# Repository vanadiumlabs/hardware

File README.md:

hardware
========

Boards, parts and firmware

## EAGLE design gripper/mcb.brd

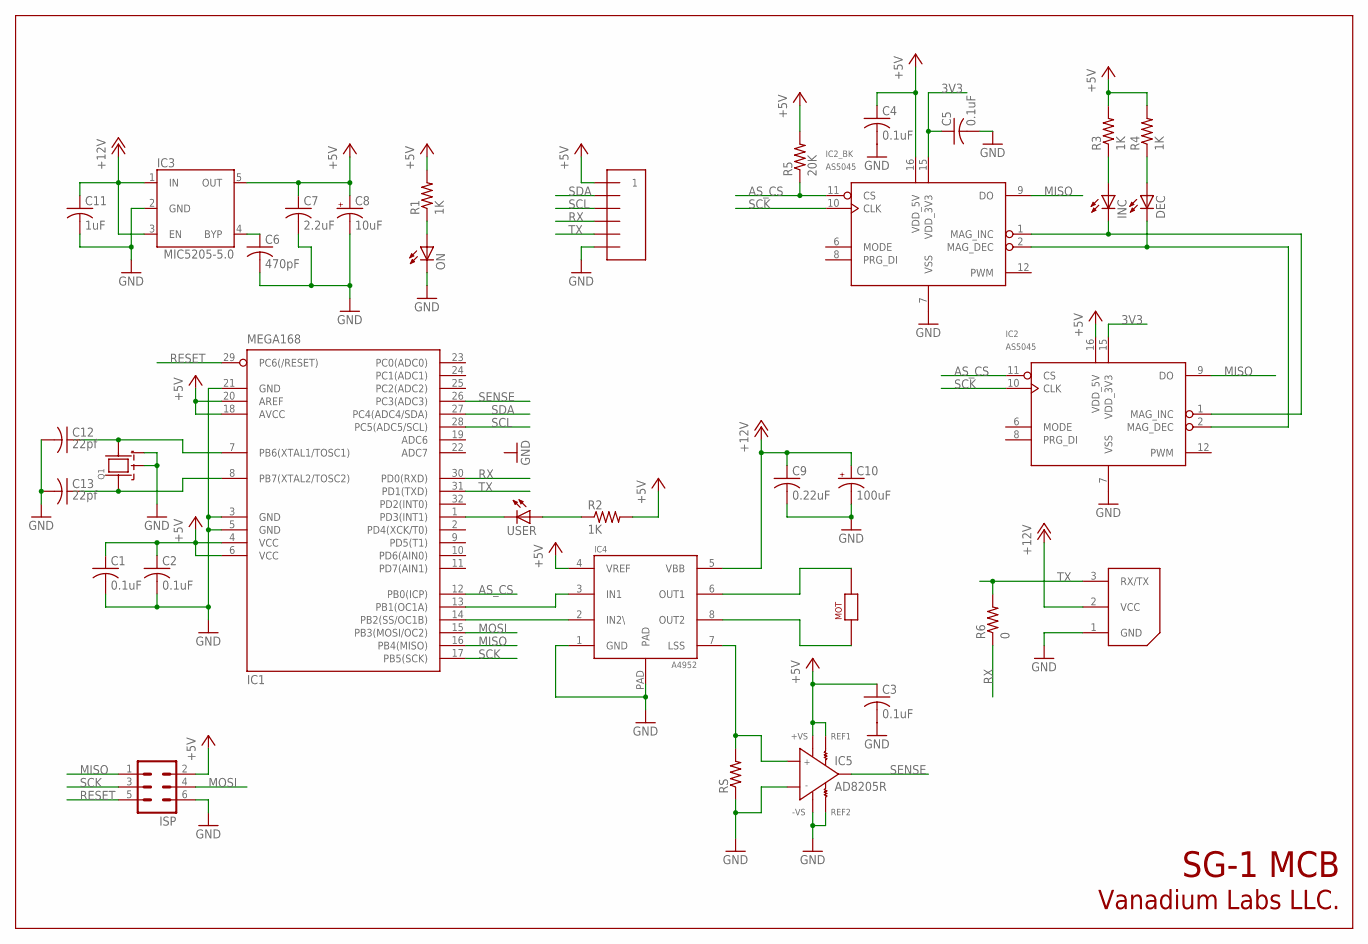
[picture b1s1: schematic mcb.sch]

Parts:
C1, C2, C3, C4, C5: 0.1uF; C0603
C6: 470pF; C0603
C7: 2.2uF; C0603
C8: 10uF; PANASONIC_B
C9: 0.22uF; C0603
C10: 100uF; PANASONIC_B
C11: 1uF; C0603
C12, C13: 22pf; C0603
DEC: LEDCHIPLED_0603; CHIPLED_0603
IC1: MEGA168; TQFP32-08
IC2, IC2_BK: AS5045; SSOP16
IC3: MIC5205-5.0; SOT-23-5
IC4: A4952; SOIC8TP
IC5: AD8205R; SO8
INC: LEDCHIPLED_0603; CHIPLED_0603
ISP: MA03-2
MOT: JUMPER; 2-PIN
ON: LEDCHIPLED_0603; CHIPLED_0603
Q1: 16MHZ; 4LCC
R1, R2, R3, R4: 1K; R0603
R5: 20K; R0603
R6: 0; R0603
RS: R-US_R1206; R1206
U$2: HEADER6; 1X6
U$5: AX-12; WM18887-ND
USER: LEDCHIPLED_0603; CHIPLED_0603

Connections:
3V3: C5.1, IC2.15 (VDD_3V3), IC2_BK.15 (VDD_3V3)
+5V: C1.1, C2.1, C3.1, C4.1, C7.1, C8.+, IC1.4 (VCC), IC1.6 (VCC), IC1.18 (AVCC), IC1.20 (AREF), IC2.16 (VDD_5V), IC2_BK.16 (VDD_5V), IC3.5 (OUT), IC4.4 (VREF), IC5.6 (+VS), IC5.7 (REF1), ISP.2, R1.2, R2.2, R3.2, R4.2, R5.2, U$2.P$1 (1)
+12V: C9.1, C10.+, C11.1, IC3.1 (IN), IC3.3 (EN), IC4.5 (VBB), U$5.2 (VCC)
AS_CS: IC1.12 (PB0(ICP)), IC2.11 (CS), IC2_BK.11 (CS), R5.1
GND: C1.2, C2.2, C3.2, C4.2, C5.2, C6.2, C7.2, C8.-, C9.2, C10.-, C11.2, C12.2, C13.2, IC1.3 (GND), IC1.5 (GND), IC1.21 (GND), IC2.7 (VSS), IC2_BK.7 (VSS), IC3.2 (GND), IC4.1 (GND), IC4.PAD, IC5.1 (IN-), IC5.2 (-VS), IC5.3 (REF2), ISP.6, ON.C, Q1.2 (G1), Q1.4 (G2), RS.1, U$2.P$6, U$5.1 (GND)
MISO: IC1.16 (PB4(MISO)), IC2.9 (DO), IC2_BK.9 (DO), ISP.1
MOSI: IC1.15 (PB3(MOSI/OC2)), ISP.4
unnamed: IC4.6 (OUT1), MOT.P$2
unnamed: IC4.8 (OUT2), MOT.P$1
unnamed: IC4.7 (LSS), IC5.8 (IN+), RS.2
unnamed: IC1.1 (PD3(INT1)), USER.C
unnamed: IC2.1 (MAG_INC), IC2_BK.1 (MAG_INC), INC.C
unnamed: DEC.C, IC2.2 (MAG_DEC), IC2_BK.2 (MAG_DEC)
unnamed: INC.A, R3.1
unnamed: DEC.A, R4.1
unnamed: C12.1, IC1.7 (PB6(XTAL1/TOSC1)), Q1.3
unnamed: C13.1, IC1.8 (PB7(XTAL2/TOSC2)), Q1.1
unnamed: IC1.14 (PB2(SS/OC1B)), IC4.2 (IN2\)
unnamed: ON.A, R1.1
unnamed: R2.1, USER.A
unnamed: IC1.13 (PB1(OC1A)), IC4.3 (IN1)
unnamed: C6.1, IC3.4 (BYP)
RESET: IC1.29 (PC6(/RESET)), ISP.5
RX: IC1.30 (PD0(RXD)), R6.1, U$2.P$4
SCK: IC1.17 (PB5(SCK)), IC2.10 (CLK), IC2_BK.10 (CLK), ISP.3
SCL: IC1.28 (PC5(ADC5/SCL)), U$2.P$3
SDA: IC1.27 (PC4(ADC4/SDA)), U$2.P$2
SENSE: IC1.26 (PC3(ADC3)), IC5.5 (OUT)
TX: IC1.31 (PD1(TXD)), R6.2, U$2.P$5, U$5.3 (RX/TX)

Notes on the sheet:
Vanadium Labs LLC.
SG-1 MCB

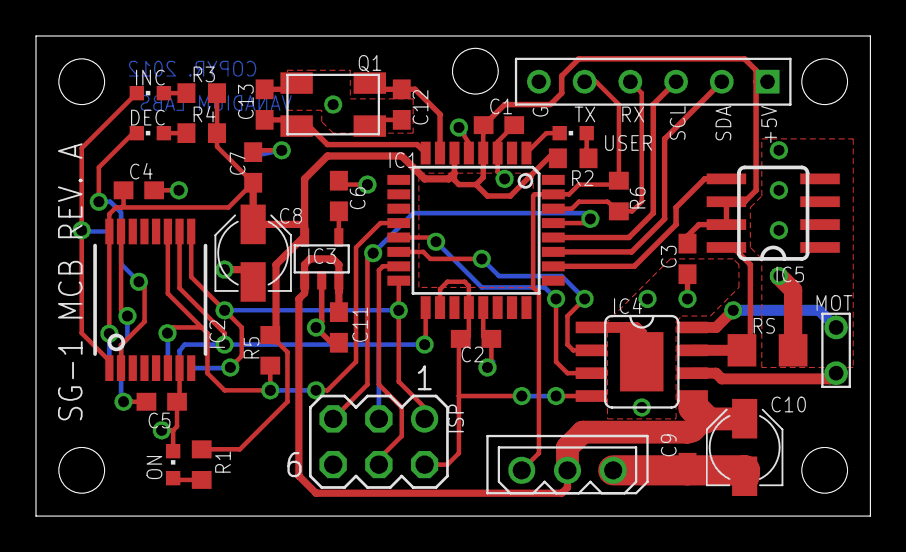
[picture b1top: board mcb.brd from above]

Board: 2 copper layers, 46.4 x 26.7 mm, 35 parts (1 on the bottom side), 29 nets.

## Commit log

2013-02-02 import from svn
2014-07-02 check in old arbotix design
2014-07-02 check in commander design
2014-07-02 check in rxbridge design
2014-07-02 check in servostik design
2014-07-04 add board layout and BOM
2014-07-04 add a readme for the ax-m1
2014-07-04 add readme
2014-07-04 add license
2014-07-04 check in rev B and gerbers
2014-09-29 add schematic and board
2014-09-29 release never-produced arbotix2
2018-04-03 check in rev.B as of Sept 29, 2014
2018-04-03 add arbotix+, last updated Sept 10, 2012
